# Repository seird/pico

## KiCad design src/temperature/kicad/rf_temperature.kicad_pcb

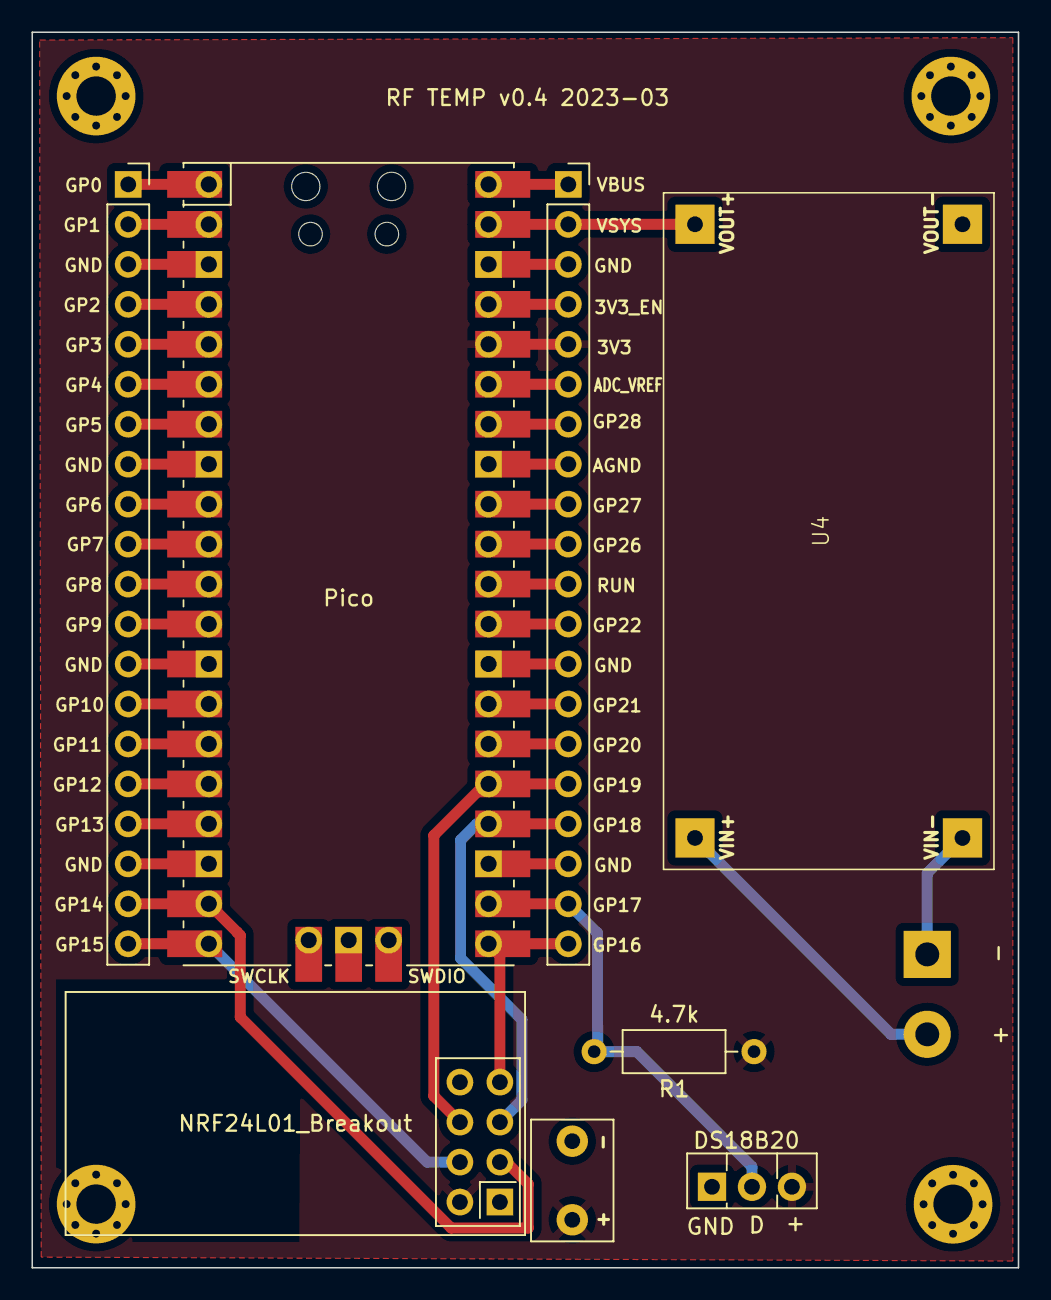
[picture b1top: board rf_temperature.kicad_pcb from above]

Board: 2 copper layers, 62.7 x 78.5 mm, 13 parts (1 on the bottom side), 36 nets.

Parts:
C1: C; C_Disc_D7.5mm_W5.0mm_P5.00mm
H1, H2, H3, H5: MountingHole_Pad; MountingHole_2.5mm_Pad_Via
J1, J3: Conn_01x20; PinSocket_1x20_P2.54mm_Vertical
J2: Screw_Terminal_01x02; TerminalBlock_bornier-2_P5.08mm
R1: 4.7k; R_Axial_DIN0207_L6.3mm_D2.5mm_P10.16mm_Horizontal
U1: Pico; RPi_Pico_SMD_TH
U2: DS18B20; TO-126-3_Vertical
U3: NRF24L01_Breakout; nRF24L01_Breakout
U4: my_LM2596AdjBuck

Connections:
3V3: C1.1, J3.5, R1.1, U1.36 (3V3), U2.3 (V_{DD}), U3.2 (VCC)
GND: C1.2, H1.1, H2.1, H3.1, H5.1, J1.3, J1.8, J1.13, J1.18, J3.3, J3.13, J3.18, U1.3 (GND), U1.8 (GND), U1.13 (GND), U1.18 (GND), U1.23 (GND), U1.28 (GND), U1.38 (GND), U2.1 (GND), U3.1 (GND), U4.4 (Vout-)
unnamed: J1.1, U1.1 (GPIO0)
unnamed: J1.2, U1.2 (GPIO1)
unnamed: J1.4, U1.4 (GPIO2)
unnamed: J1.5, U1.5 (GPIO3)
unnamed: J1.6, U1.6 (GPIO4)
unnamed: J1.7, U1.7 (GPIO5)
unnamed: J1.9, U1.9 (GPIO6)
unnamed: J1.10, U1.10 (GPIO7)
unnamed: J1.11, U1.11 (GPIO8)
unnamed: J1.12, U1.12 (GPIO9)
unnamed: J1.14, U1.14 (GPIO10)
unnamed: J1.15, U1.15 (GPIO11)
unnamed: J1.16, U1.16 (GPIO12)
unnamed: J1.17, U1.17 (GPIO13)
unnamed: J1.19, U1.19 (GPIO14), U3.3 (CE)
unnamed: J1.20, U1.20 (GPIO15), U3.4 (~CSN)
unnamed: J2.1, U4.2 (Vin-)
unnamed: J2.2, U4.1 (Vin+)
unnamed: J3.1, U1.40 (VBUS)
unnamed: J3.2, U1.39 (VSYS), U4.3 (Vout+)
unnamed: J3.4, U1.37 (3V3_EN)
unnamed: J3.6, U1.35 (ADC_VREF)
unnamed: J3.7, U1.34 (GPIO28_ADC2)
unnamed: J3.8, U1.33 (AGND)
unnamed: J3.9, U1.32 (GPIO27_ADC1)
unnamed: J3.10, U1.31 (GPIO26_ADC0)
unnamed: J3.11, U1.30 (RUN)
unnamed: J3.12, U1.29 (GPIO22)
unnamed: J3.14, U1.27 (GPIO21)
unnamed: J3.15, U1.26 (GPIO20)
unnamed: J3.16, U1.25 (GPIO19), U3.6 (MOSI)
unnamed: J3.17, U1.24 (GPIO18), U3.5 (SCK)
unnamed: J3.19, R1.2, U1.22 (GPIO17), U2.2 (DQ)
unnamed: J3.20, U1.21 (GPIO16), U3.7 (MISO)

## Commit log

2022-11-20 add parameters to cmakelists
2022-11-30 restructure
2023-03-04 add basic kicad design
2023-03-25 use ground plane
2023-03-25 cleanup
2023-03-25 update temperature sensor data pin
2023-03-25 Pin.pull
2023-04-30 burst
2023-10-08 relay switch
2023-10-08 copper keepout
2023-10-08 hid-inout
2023-10-22 add some tinyusb toy examples
2023-11-06 burst & debounce
